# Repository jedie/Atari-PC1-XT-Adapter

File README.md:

# Atari PC XT-Adapter

A XT-Bus Adapter for the old Atari PC1

## PCB

Test size via print:

## Current Schema

## References

* "Atari PC ISA Bridge" PDF from http://www.ataripc.net/document-archive/

## Links

* https://atariage.com/forums/topic/315266-atari-pc1-isa-expansion-adapter-j2-j8-pinout/ (en)
* https://forum.classic-computing.de/forum/index.php?thread/24929-atari-pc1-externe-floppy-interner-isa-bus/ (de)

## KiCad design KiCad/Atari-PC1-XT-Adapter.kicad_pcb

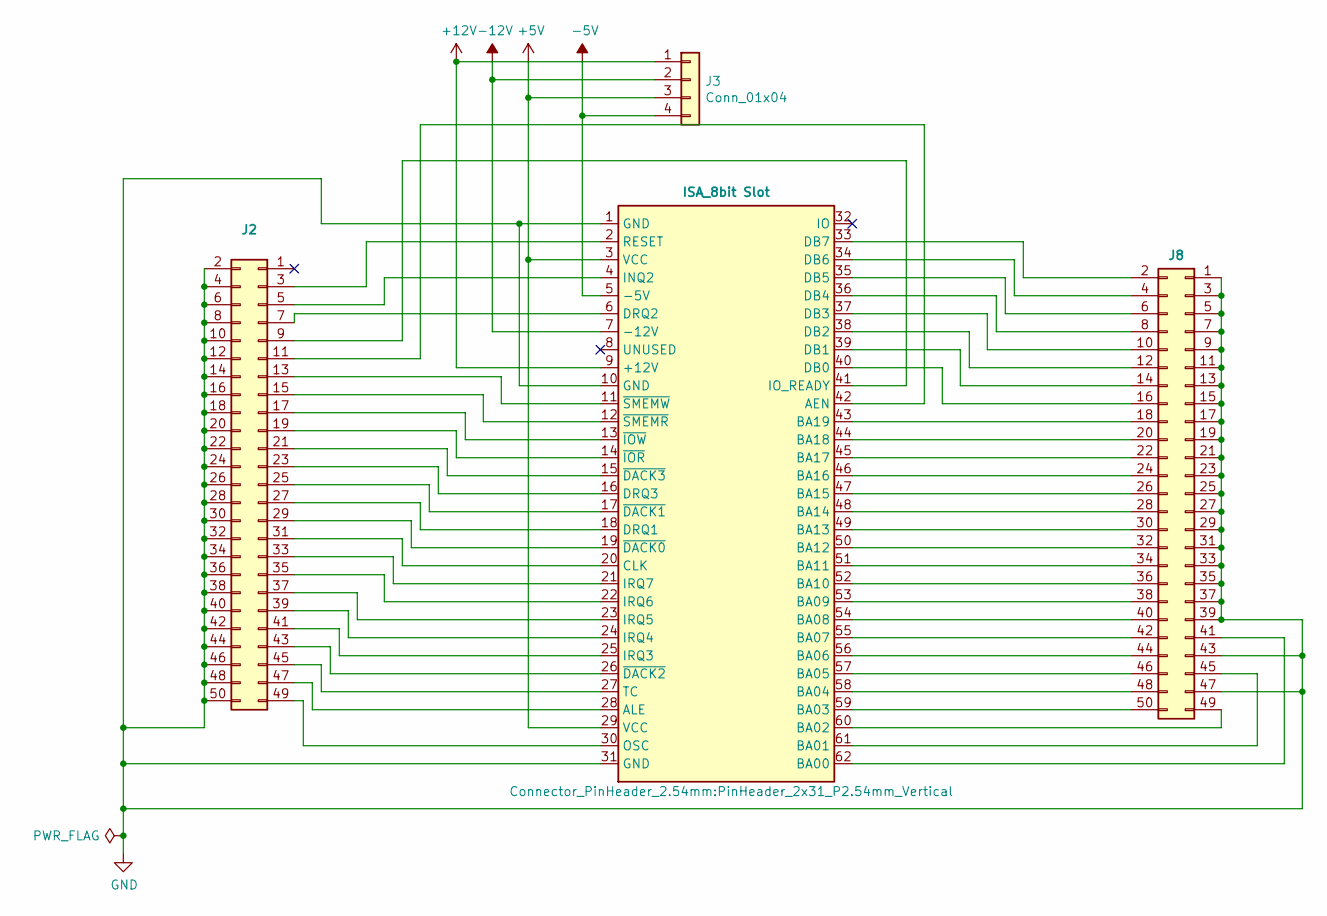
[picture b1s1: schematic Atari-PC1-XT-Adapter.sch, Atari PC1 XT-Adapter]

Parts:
J1: ISA_8bit Slot; PinHeader_2x31_P2.54mm_Vertical
J2, J8: Conn_2Rows-49Pins; PinHeader_2x25_P2.54mm_Vertical
J3: Conn_01x04; PinHeader_1x04_P2.54mm_Vertical

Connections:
GND: J1.1 (GND), J1.10 (GND), J1.31 (GND), J2.2, J2.4, J2.6, J2.8, J2.10, J2.12, J2.14, J2.16, J2.18, J2.20, J2.22, J2.24, J2.26, J2.28, J2.30, J2.32, J2.34, J2.36, J2.38, J2.40, J2.42, J2.44, J2.46, J2.48, J2.50, J8.1, J8.3, J8.5, J8.7, J8.9, J8.11, J8.13, J8.15, J8.17, J8.19, J8.21, J8.23, J8.25, J8.27, J8.29, J8.31, J8.33, J8.35, J8.37, J8.39, J8.43, J8.47
unnamed: J1.2 (RESET), J2.3
unnamed: J1.4 (INQ2), J2.5
unnamed: J1.6 (DRQ2), J2.7
unnamed: J1.11 (~SMEMW), J2.13
unnamed: J1.12 (~SMEMR), J2.15
unnamed: J1.13 (~IOW), J2.17
unnamed: J1.14 (~IOR), J2.19
unnamed: J1.15 (~DACK3), J2.21
unnamed: J1.16 (DRQ3), J2.23
unnamed: J1.17 (~DACK1), J2.25
unnamed: J1.18 (DRQ1), J2.27
unnamed: J1.19 (~DACK0), J2.29
unnamed: J1.20 (CLK), J2.31
unnamed: J1.21 (IRQ7), J2.33
unnamed: J1.22 (IRQ6), J2.35
unnamed: J1.23 (IRQ5), J2.37
unnamed: J1.24 (IRQ4), J2.39
unnamed: J1.25 (IRQ3), J2.41
unnamed: J1.26 (~DACK2), J2.43
unnamed: J1.27 (TC), J2.45
unnamed: J1.28 (ALE), J2.47
unnamed: J1.30 (OSC), J2.49
unnamed: J1.33 (DB7), J8.2
unnamed: J1.34 (DB6), J8.4
unnamed: J1.35 (DB5), J8.6
unnamed: J1.36 (DB4), J8.8
unnamed: J1.37 (DB3), J8.10
unnamed: J1.38 (DB2), J8.12
unnamed: J1.39 (DB1), J8.14
unnamed: J1.40 (DB0), J8.16
unnamed: J1.41 (IO_READY), J2.9
unnamed: J1.42 (AEN), J2.11
unnamed: J1.43 (BA19), J8.18
unnamed: J1.44 (BA18), J8.20
unnamed: J1.45 (BA17), J8.22
unnamed: J1.46 (BA16), J8.24
unnamed: J1.47 (BA15), J8.26
unnamed: J1.48 (BA14), J8.28
unnamed: J1.49 (BA13), J8.30
unnamed: J1.50 (BA12), J8.32
unnamed: J1.51 (BA11), J8.34
unnamed: J1.52 (BA10), J8.36
unnamed: J1.53 (BA09), J8.38
unnamed: J1.54 (BA08), J8.40
unnamed: J1.55 (BA07), J8.42
unnamed: J1.56 (BA06), J8.44
unnamed: J1.57 (BA05), J8.46
unnamed: J1.58 (BA04), J8.48
unnamed: J1.59 (BA03), J8.50
unnamed: J1.60 (BA02), J8.49
unnamed: J1.61 (BA01), J8.45
unnamed: J1.62 (BA00), J8.41

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
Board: 2 copper layers, 4 parts (0 on the bottom side), 57 nets, no tracks yet.

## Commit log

2021-07-22 Add current state
2021-07-30 Add Floppy Connection KiCad files
2021-08-03 Shugart vs. PC34 connection
2021-08-04 PWR_FLAG to GND
2021-08-22 Update Floppy Connection
2021-08-22 Update XT-Adapter
2021-09-02 Update PCB
2021-09-02 add print test image
